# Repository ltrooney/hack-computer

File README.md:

The implementation files of the Hack Computer system. This current implementation uses the build instructions in the book The Elements of Computing Systems, by Noam Nisan and Shimon Schocken.

Programming languages used for: Hardware -> Hardware Description Language (HDL) --- Assembler, Virtual Machine (VM), and Compiler -> Java --- Operating System -> Jack

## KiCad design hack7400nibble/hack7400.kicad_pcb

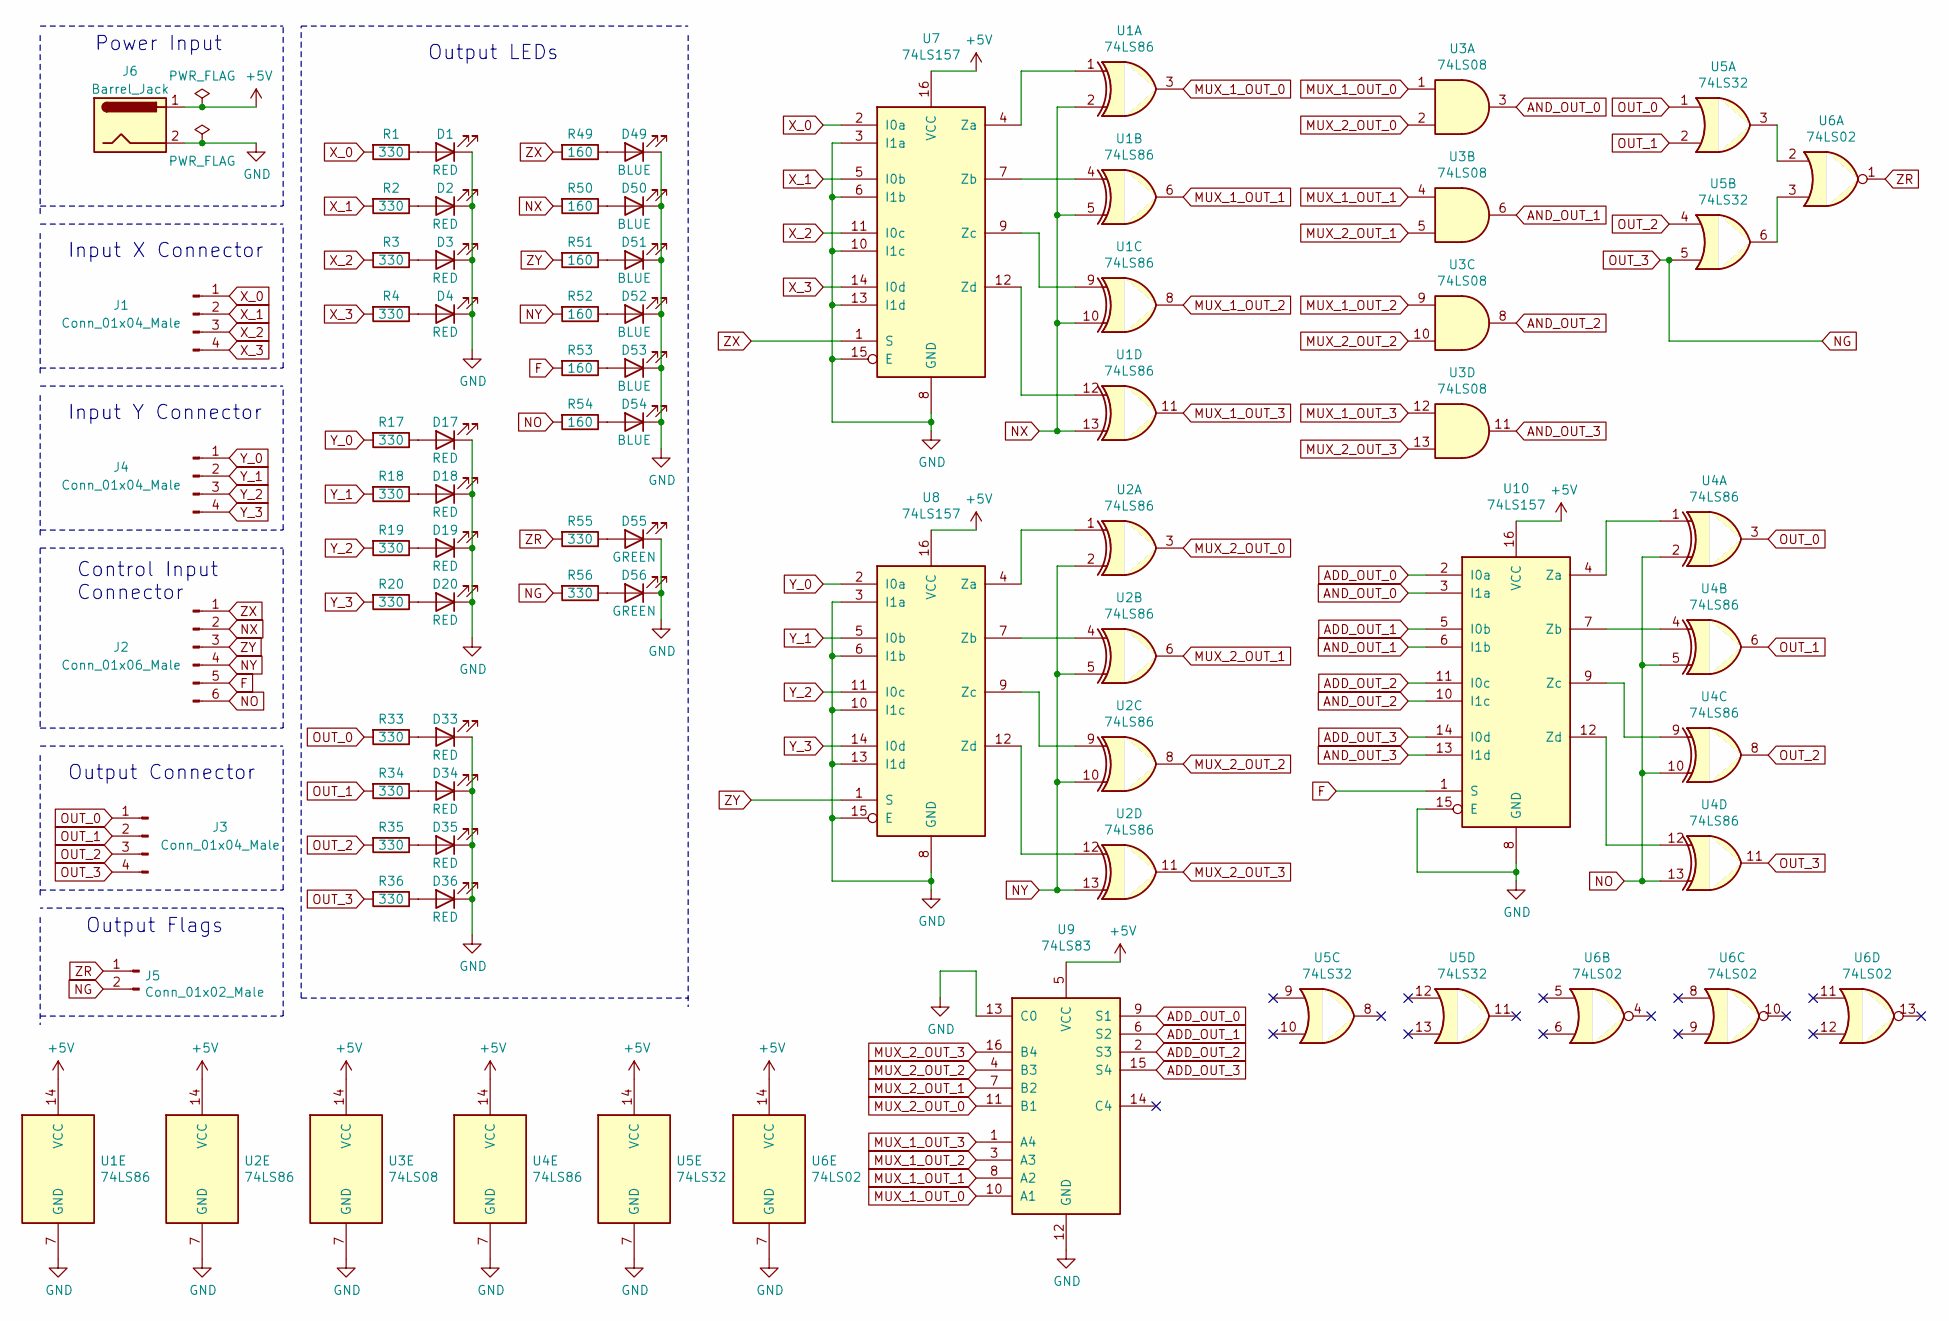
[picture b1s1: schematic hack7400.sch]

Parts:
D1, D2, D3, D4, D17, D18, D19, D20, D33, D34, D35, D36: RED; LED_D3.0mm
D49, D50, D51, D52, D53, D54: BLUE; LED_D3.0mm
D55, D56: GREEN; LED_D3.0mm
J1, J3, J4: Conn_01x04_Male; PinHeader_1x04_P2.54mm_Vertical
J2: Conn_01x06_Male; PinHeader_1x06_P2.54mm_Vertical
J5: Conn_01x02_Male; PinHeader_1x02_P2.54mm_Vertical
J6: Barrel_Jack; BarrelJack_CUI_PJ-102AH_Horizontal
R1, R2, R3, R4, R17, R18, R19, R20, R33, R34, R35, R36, R55, R56: 330; R_Axial_DIN0207_L6.3mm_D2.5mm_P7.62mm_Horizontal
R49, R50, R51, R52, R53, R54: 160; R_Axial_DIN0207_L6.3mm_D2.5mm_P7.62mm_Horizontal
U1, U2, U4: 74LS86; DIP-14_W7.62mm_Socket
U3: 74LS08; DIP-14_W7.62mm_Socket
U5: 74LS32; DIP-14_W7.62mm_Socket
U6: 74LS02; DIP-14_W7.62mm_Socket
U7, U8, U10: 74LS157; DIP-16_W7.62mm_Socket
U9: 74LS83; DIP-16_W7.62mm_Socket

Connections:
+5V: J6.1, U1.14 (VCC), U2.14 (VCC), U3.14 (VCC), U4.14 (VCC), U5.14 (VCC), U6.14 (VCC), U7.16 (VCC), U8.16 (VCC), U9.5 (VCC), U10.16 (VCC)
ADD_OUT_0: U9.9 (S1), U10.2 (I0a)
ADD_OUT_1: U9.6 (S2), U10.5 (I0b)
ADD_OUT_2: U9.2 (S3), U10.11 (I0c)
ADD_OUT_3: U9.15 (S4), U10.14 (I0d)
AND_OUT_0: U3.3, U10.3 (I1a)
AND_OUT_1: U3.6, U10.6 (I1b)
AND_OUT_2: U3.8, U10.10 (I1c)
AND_OUT_3: U3.11, U10.13 (I1d)
F: J2.5, R53.2, U10.1 (S)
GND: D1.1 (K), D2.1 (K), D3.1 (K), D4.1 (K), D17.1 (K), D18.1 (K), D19.1 (K), D20.1 (K), D33.1 (K), D34.1 (K), D35.1 (K), D36.1 (K), D49.1 (K), D50.1 (K), D51.1 (K), D52.1 (K), D53.1 (K), D54.1 (K), D55.1 (K), D56.1 (K), J6.2, U1.7 (GND), U2.7 (GND), U3.7 (GND), U4.7 (GND), U5.7 (GND), U6.7 (GND), U7.3 (I1a), U7.6 (I1b), U7.8 (GND), U7.10 (I1c), U7.13 (I1d), U7.15 (E), U8.3 (I1a), U8.6 (I1b), U8.8 (GND), U8.10 (I1c), U8.13 (I1d), U8.15 (E), U9.12 (GND), U9.13 (C0), U10.8 (GND), U10.15 (E)
MUX_1_OUT_0: U1.3, U3.1, U9.10 (A1)
MUX_1_OUT_1: U1.6, U3.4, U9.8 (A2)
MUX_1_OUT_2: U1.8, U3.9, U9.3 (A3)
MUX_1_OUT_3: U1.11, U3.12, U9.1 (A4)
MUX_2_OUT_0: U2.3, U3.2, U9.11 (B1)
MUX_2_OUT_1: U2.6, U3.5, U9.7 (B2)
MUX_2_OUT_2: U2.8, U3.10, U9.4 (B3)
MUX_2_OUT_3: U2.11, U3.13, U9.16 (B4)
NG: J3.4, J5.2, R36.2, R56.2, U4.11, U5.5
NO: J2.6, R54.2, U4.2, U4.5, U4.10, U4.13
NX: J2.2, R50.2, U1.2, U1.5, U1.10, U1.13
NY: J2.4, R52.2, U2.2, U2.5, U2.10, U2.13
unnamed: D1.2 (A), R1.1
unnamed: D2.2 (A), R2.1
unnamed: D3.2 (A), R3.1
unnamed: D4.2 (A), R4.1
unnamed: D17.2 (A), R17.1
unnamed: D18.2 (A), R18.1
unnamed: D19.2 (A), R19.1
unnamed: D20.2 (A), R20.1
unnamed: D33.2 (A), R33.1
unnamed: D34.2 (A), R34.1
unnamed: D35.2 (A), R35.1
unnamed: D36.2 (A), R36.1
unnamed: D49.2 (A), R49.1
unnamed: D50.2 (A), R50.1
unnamed: D51.2 (A), R51.1
unnamed: D52.2 (A), R52.1
unnamed: D53.2 (A), R53.1
unnamed: D54.2 (A), R54.1
unnamed: D55.2 (A), R55.1
unnamed: D56.2 (A), R56.1
unnamed: U1.1, U7.4 (Za)
unnamed: U1.4, U7.7 (Zb)
unnamed: U1.9, U7.9 (Zc)
unnamed: U1.12, U7.12 (Zd)
unnamed: U2.1, U8.4 (Za)
unnamed: U2.4, U8.7 (Zb)
unnamed: U2.9, U8.9 (Zc)
unnamed: U2.12, U8.12 (Zd)
unnamed: U5.3, U6.2
unnamed: U5.6, U6.3
unnamed: U4.1, U10.4 (Za)
unnamed: U4.4, U10.7 (Zb)
unnamed: U4.9, U10.9 (Zc)
unnamed: U4.12, U10.12 (Zd)
OUT_0: J3.1, R33.2, U4.3, U5.1
OUT_1: J3.2, R34.2, U4.6, U5.2
OUT_2: J3.3, R35.2, U4.8, U5.4
X_0: J1.1, R1.2, U7.2 (I0a)
X_1: J1.2, R2.2, U7.5 (I0b)
X_2: J1.3, R3.2, U7.11 (I0c)
X_3: J1.4, R4.2, U7.14 (I0d)
Y_0: J4.1, R17.2, U8.2 (I0a)
Y_1: J4.2, R18.2, U8.5 (I0b)
Y_2: J4.3, R19.2, U8.11 (I0c)
Y_3: J4.4, R20.2, U8.14 (I0d)
ZR: J5.1, R55.2, U6.1
ZX: J2.1, R49.2, U7.1 (S)
ZY: J2.3, R51.2, U8.1 (S)

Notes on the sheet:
Input X Connector
Control Input Connector
Output Flags
Output LEDs
Power Input
Input Y Connector
Output Connector

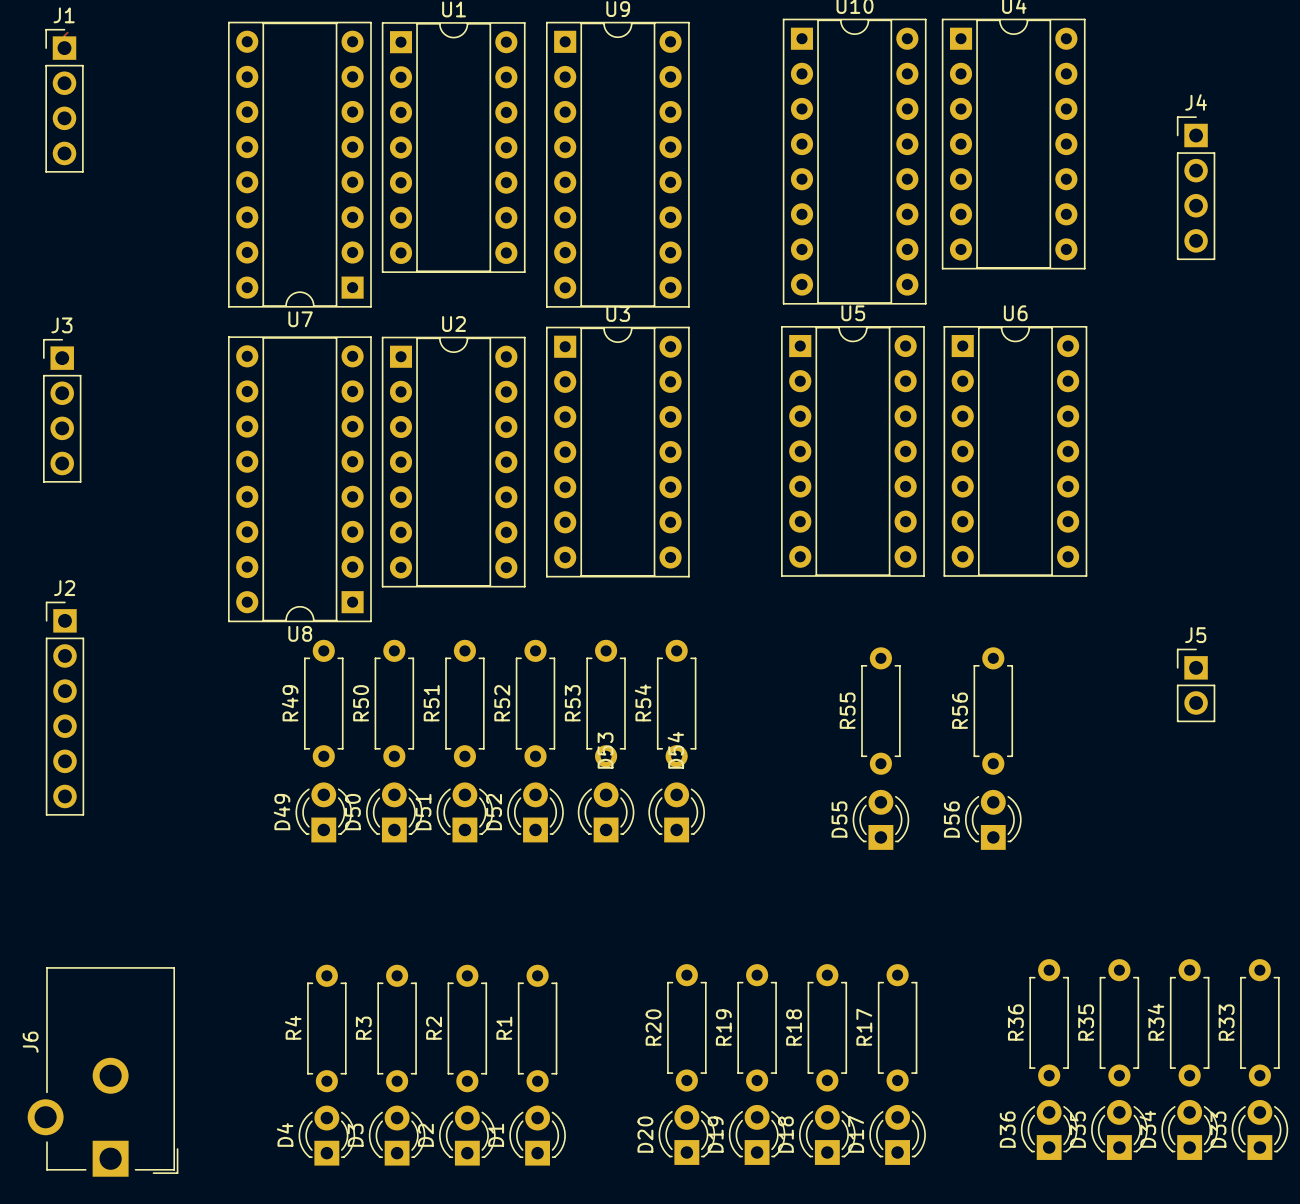
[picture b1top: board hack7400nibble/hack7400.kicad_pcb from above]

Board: 2 copper layers, 56 parts (0 on the bottom side), 71 nets.

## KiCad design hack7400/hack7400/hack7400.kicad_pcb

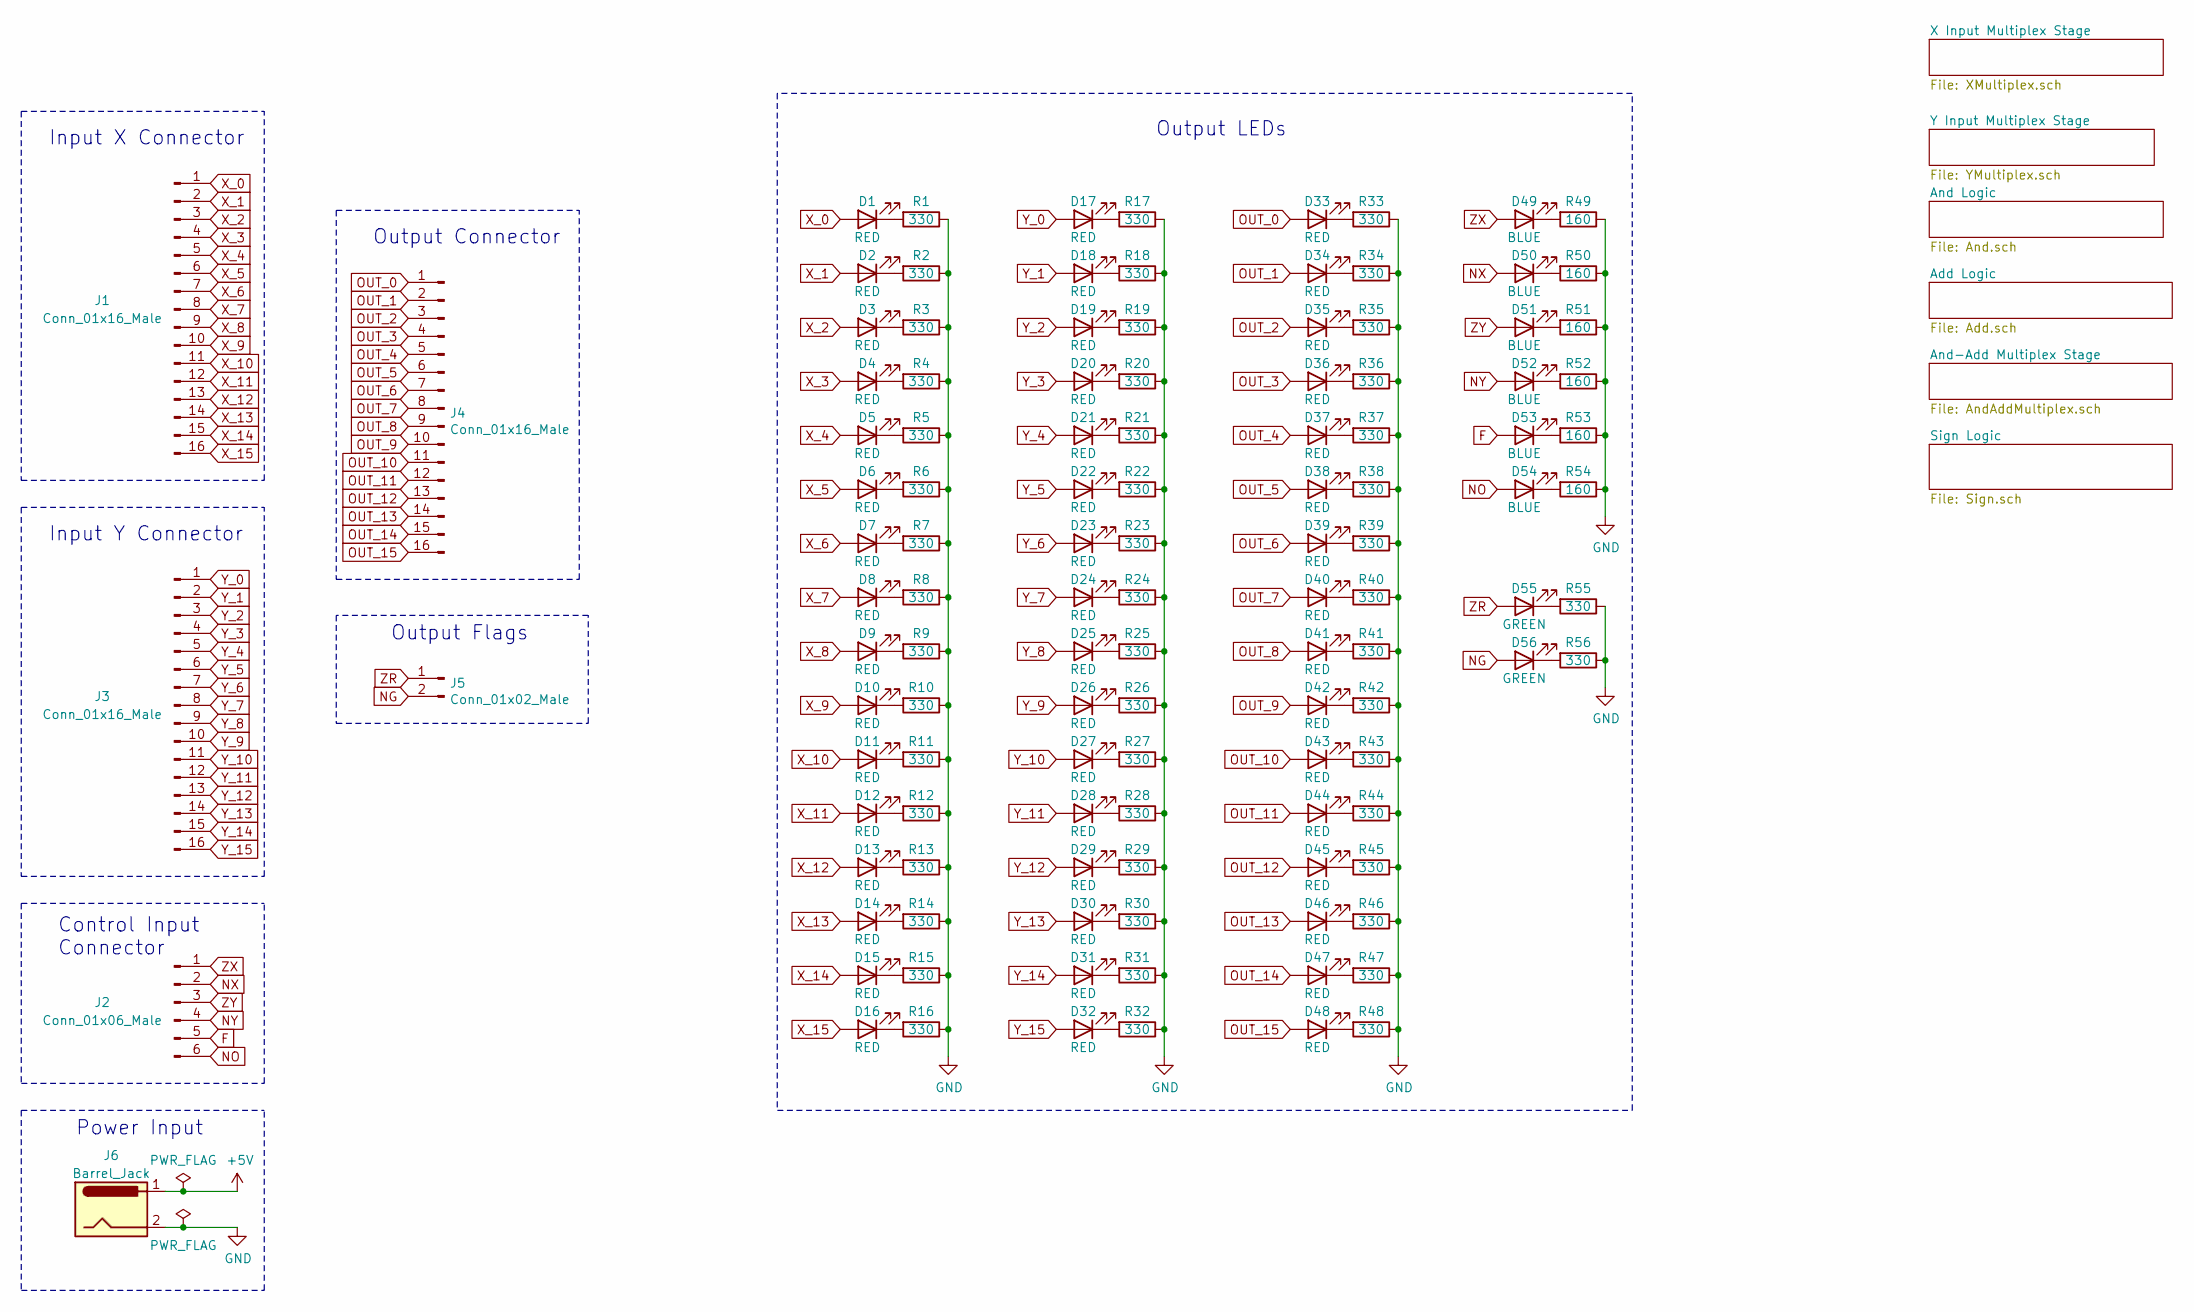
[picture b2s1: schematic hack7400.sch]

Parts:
D1, D2, D3, D4, D5, D6, D7, D8, D9, D10, D11, D12, D13, D14, D15, D16, D17, D18, D19, D20, D21, D22, D23, D24, D25, D26, D27, D28, D29, D30, D31, D32, D33, D34, D35, D36, D37, D38, D39, D40, D41, D42, D43, D44, D45, D46, D47, D48: RED; LED_D3.0mm
D49, D50, D51, D52, D53, D54: BLUE; LED_D3.0mm
D55, D56: GREEN; LED_D3.0mm
J1, J3, J4: Conn_01x16_Male; IDC-Header_2x08_P2.54mm_Vertical
J2: Conn_01x06_Male; PinHeader_1x06_P2.54mm_Vertical
J5: Conn_01x02_Male; PinHeader_1x02_P2.54mm_Vertical
J6: Barrel_Jack; BarrelJack_CUI_PJ-102AH_Horizontal
R1, R2, R3, R4, R5, R6, R7, R8, R9, R10, R11, R12, R13, R14, R15, R16, R17, R18, R19, R20, R21, R22, R23, R24, R25, R26, R27, R28, R29, R30, R31, R32, R33, R34, R35, R36, R37, R38, R39, R40, R41, R42, R43, R44, R45, R46, R47, R48, R55, R56: 330; R_Axial_DIN0207_L6.3mm_D2.5mm_P7.62mm_Horizontal
R49, R50, R51, R52, R53, R54: 160; R_Axial_DIN0207_L6.3mm_D2.5mm_P7.62mm_Horizontal

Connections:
+5V: J6.1; also elsewhere on the board
F: D53.2 (A), J2.5; also elsewhere on the board
GND: J6.2, R1.1, R2.1, R3.1, R4.1, R5.1, R6.1, R7.1, R8.1, R9.1, R10.1, R11.1, R12.1, R13.1, R14.1, R15.1, R16.1, R17.1, R18.1, R19.1, R20.1, R21.1, R22.1, R23.1, R24.1, R25.1, R26.1, R27.1, R28.1, R29.1, R30.1, R31.1, R32.1, R33.1, R34.1, R35.1, R36.1, R37.1, R38.1, R39.1, R40.1, R41.1, R42.1, R43.1, R44.1, R45.1, R46.1, R47.1, R48.1, R49.1, R50.1, R51.1, R52.1, R53.1, R54.1, R55.1, R56.1; also elsewhere on the board
NG: D48.2 (A), D56.2 (A), J4.16, J5.2; also elsewhere on the board
NO: D54.2 (A), J2.6; also elsewhere on the board
NX: D50.2 (A), J2.2; also elsewhere on the board
NY: D52.2 (A), J2.4; also elsewhere on the board
unnamed: D1.1 (K), R1.2
unnamed: D2.1 (K), R2.2
unnamed: D3.1 (K), R3.2
unnamed: D4.1 (K), R4.2
unnamed: D5.1 (K), R5.2
unnamed: D6.1 (K), R6.2
unnamed: D7.1 (K), R7.2
unnamed: D8.1 (K), R8.2
unnamed: D9.1 (K), R9.2
unnamed: D10.1 (K), R10.2
unnamed: D11.1 (K), R11.2
unnamed: D12.1 (K), R12.2
unnamed: D13.1 (K), R13.2
unnamed: D14.1 (K), R14.2
unnamed: D15.1 (K), R15.2
unnamed: D16.1 (K), R16.2
unnamed: D17.1 (K), R17.2
unnamed: D18.1 (K), R18.2
unnamed: D19.1 (K), R19.2
unnamed: D20.1 (K), R20.2
unnamed: D21.1 (K), R21.2
unnamed: D22.1 (K), R22.2
unnamed: D23.1 (K), R23.2
unnamed: D24.1 (K), R24.2
unnamed: D25.1 (K), R25.2
unnamed: D26.1 (K), R26.2
unnamed: D27.1 (K), R27.2
unnamed: D28.1 (K), R28.2
unnamed: D29.1 (K), R29.2
unnamed: D30.1 (K), R30.2
unnamed: D31.1 (K), R31.2
unnamed: D32.1 (K), R32.2
unnamed: D33.1 (K), R33.2
unnamed: D34.1 (K), R34.2
unnamed: D35.1 (K), R35.2
unnamed: D36.1 (K), R36.2
unnamed: D37.1 (K), R37.2
unnamed: D38.1 (K), R38.2
unnamed: D39.1 (K), R39.2
unnamed: D40.1 (K), R40.2
unnamed: D41.1 (K), R41.2
unnamed: D42.1 (K), R42.2
unnamed: D43.1 (K), R43.2
unnamed: D44.1 (K), R44.2
unnamed: D45.1 (K), R45.2
unnamed: D46.1 (K), R46.2
unnamed: D47.1 (K), R47.2
unnamed: D48.1 (K), R48.2
unnamed: D49.1 (K), R49.2
unnamed: D50.1 (K), R50.2
unnamed: D51.1 (K), R51.2
unnamed: D52.1 (K), R52.2
unnamed: D53.1 (K), R53.2
unnamed: D54.1 (K), R54.2
unnamed: D55.1 (K), R55.2
unnamed: D56.1 (K), R56.2
OUT_0: D33.2 (A), J4.1; also elsewhere on the board
OUT_1: D34.2 (A), J4.2; also elsewhere on the board
OUT_2: D35.2 (A), J4.3; also elsewhere on the board
OUT_3: D36.2 (A), J4.4; also elsewhere on the board
OUT_4: D37.2 (A), J4.5; also elsewhere on the board
OUT_5: D38.2 (A), J4.6; also elsewhere on the board
OUT_6: D39.2 (A), J4.7; also elsewhere on the board
OUT_7: D40.2 (A), J4.8; also elsewhere on the board
OUT_8: D41.2 (A), J4.9; also elsewhere on the board
OUT_9: D42.2 (A), J4.10; also elsewhere on the board
OUT_10: D43.2 (A), J4.11; also elsewhere on the board
OUT_11: D44.2 (A), J4.12; also elsewhere on the board
OUT_12: D45.2 (A), J4.13; also elsewhere on the board
OUT_13: D46.2 (A), J4.14; also elsewhere on the board
OUT_14: D47.2 (A), J4.15; also elsewhere on the board
X_0: D1.2 (A), J1.1; also elsewhere on the board
X_1: D2.2 (A), J1.2; also elsewhere on the board
X_2: D3.2 (A), J1.3; also elsewhere on the board
X_3: D4.2 (A), J1.4; also elsewhere on the board
X_4: D5.2 (A), J1.5; also elsewhere on the board
X_5: D6.2 (A), J1.6; also elsewhere on the board
X_6: D7.2 (A), J1.7; also elsewhere on the board
X_7: D8.2 (A), J1.8; also elsewhere on the board
X_8: D9.2 (A), J1.9; also elsewhere on the board
X_9: D10.2 (A), J1.10; also elsewhere on the board
X_10: D11.2 (A), J1.11; also elsewhere on the board
X_11: D12.2 (A), J1.12; also elsewhere on the board
X_12: D13.2 (A), J1.13; also elsewhere on the board
X_13: D14.2 (A), J1.14; also elsewhere on the board
X_14: D15.2 (A), J1.15; also elsewhere on the board
X_15: D16.2 (A), J1.16; also elsewhere on the board
Y_0: D17.2 (A), J3.1; also elsewhere on the board
Y_1: D18.2 (A), J3.2; also elsewhere on the board
Y_2: D19.2 (A), J3.3; also elsewhere on the board
Y_3: D20.2 (A), J3.4; also elsewhere on the board
Y_4: D21.2 (A), J3.5; also elsewhere on the board
Y_5: D22.2 (A), J3.6; also elsewhere on the board
Y_6: D23.2 (A), J3.7; also elsewhere on the board
Y_7: D24.2 (A), J3.8; also elsewhere on the board
Y_8: D25.2 (A), J3.9; also elsewhere on the board
Y_9: D26.2 (A), J3.10; also elsewhere on the board
Y_10: D27.2 (A), J3.11; also elsewhere on the board
Y_11: D28.2 (A), J3.12; also elsewhere on the board
Y_12: D29.2 (A), J3.13; also elsewhere on the board
Y_13: D30.2 (A), J3.14; also elsewhere on the board
Y_14: D31.2 (A), J3.15; also elsewhere on the board
Y_15: D32.2 (A), J3.16
ZR: D55.2 (A), J5.1; also elsewhere on the board
ZX: D49.2 (A), J2.1; also elsewhere on the board
ZY: D51.2 (A), J2.3; also elsewhere on the board

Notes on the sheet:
Input X Connector
Input Y Connector
Control Input Connector
Output Connector
Output Flags
Output LEDs
Power Input

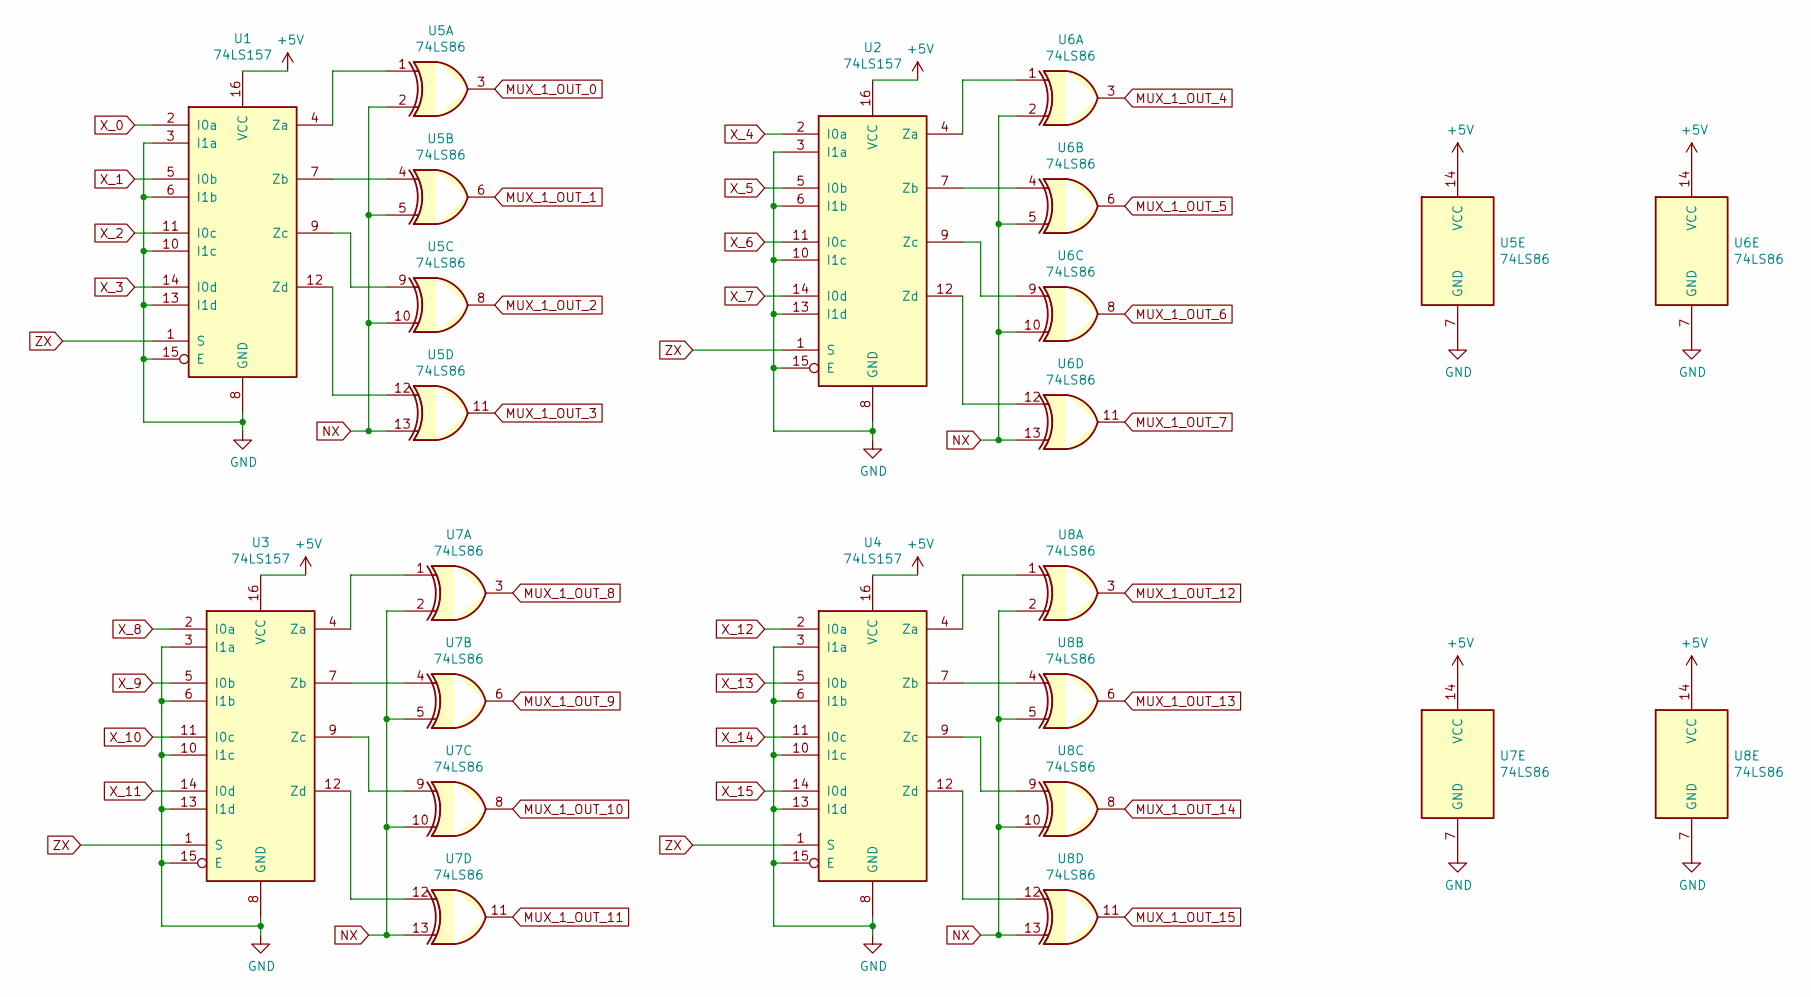
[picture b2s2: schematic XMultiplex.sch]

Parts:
U1, U2, U3, U4: 74LS157; DIP-16_W7.62mm_Socket
U5, U6, U7, U8: 74LS86; DIP-14_W7.62mm_Socket

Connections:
+5V: U1.16 (VCC), U2.16 (VCC), U3.16 (VCC), U4.16 (VCC), U5.14 (VCC), U6.14 (VCC), U7.14 (VCC), U8.14 (VCC); also elsewhere on the board
GND: U1.3 (I1a), U1.6 (I1b), U1.8 (GND), U1.10 (I1c), U1.13 (I1d), U1.15 (E), U2.3 (I1a), U2.6 (I1b), U2.8 (GND), U2.10 (I1c), U2.13 (I1d), U2.15 (E), U3.3 (I1a), U3.6 (I1b), U3.8 (GND), U3.10 (I1c), U3.13 (I1d), U3.15 (E), U4.3 (I1a), U4.6 (I1b), U4.8 (GND), U4.10 (I1c), U4.13 (I1d), U4.15 (E), U5.7 (GND), U6.7 (GND), U7.7 (GND), U8.7 (GND); also elsewhere on the board
MUX_1_OUT_0: U5.3; also elsewhere on the board
MUX_1_OUT_1: U5.6; also elsewhere on the board
MUX_1_OUT_2: U5.8; also elsewhere on the board
MUX_1_OUT_3: U5.11; also elsewhere on the board
MUX_1_OUT_4: U6.3; also elsewhere on the board
MUX_1_OUT_5: U6.6; also elsewhere on the board
MUX_1_OUT_6: U6.8; also elsewhere on the board
MUX_1_OUT_7: U6.11; also elsewhere on the board
MUX_1_OUT_8: U7.3; also elsewhere on the board
MUX_1_OUT_9: U7.6; also elsewhere on the board
MUX_1_OUT_10: U7.8; also elsewhere on the board
MUX_1_OUT_11: U7.11; also elsewhere on the board
MUX_1_OUT_12: U8.3; also elsewhere on the board
MUX_1_OUT_13: U8.6; also elsewhere on the board
MUX_1_OUT_14: U8.8; also elsewhere on the board
MUX_1_OUT_15: U8.11; also elsewhere on the board
NX: U5.2, U5.5, U5.10, U5.13, U6.2, U6.5, U6.10, U6.13, U7.2, U7.5, U7.10, U7.13, U8.2, U8.5, U8.10, U8.13; also elsewhere on the board
unnamed: U1.4 (Za), U5.1
unnamed: U1.7 (Zb), U5.4
unnamed: U1.9 (Zc), U5.9
unnamed: U1.12 (Zd), U5.12
unnamed: U2.4 (Za), U6.1
unnamed: U2.7 (Zb), U6.4
unnamed: U2.9 (Zc), U6.9
unnamed: U2.12 (Zd), U6.12
unnamed: U3.4 (Za), U7.1
unnamed: U3.7 (Zb), U7.4
unnamed: U3.9 (Zc), U7.9
unnamed: U3.12 (Zd), U7.12
unnamed: U4.4 (Za), U8.1
unnamed: U4.7 (Zb), U8.4
unnamed: U4.9 (Zc), U8.9
unnamed: U4.12 (Zd), U8.12
X_0: U1.2 (I0a); also elsewhere on the board
X_1: U1.5 (I0b); also elsewhere on the board
X_2: U1.11 (I0c); also elsewhere on the board
X_3: U1.14 (I0d); also elsewhere on the board
X_4: U2.2 (I0a); also elsewhere on the board
X_5: U2.5 (I0b); also elsewhere on the board
X_6: U2.11 (I0c); also elsewhere on the board
X_7: U2.14 (I0d); also elsewhere on the board
X_8: U3.2 (I0a); also elsewhere on the board
X_9: U3.5 (I0b); also elsewhere on the board
X_10: U3.11 (I0c); also elsewhere on the board
X_11: U3.14 (I0d); also elsewhere on the board
X_12: U4.2 (I0a); also elsewhere on the board
X_13: U4.5 (I0b); also elsewhere on the board
X_14: U4.11 (I0c); also elsewhere on the board
X_15: U4.14 (I0d); also elsewhere on the board
ZX: U1.1 (S), U2.1 (S), U3.1 (S), U4.1 (S); also elsewhere on the board

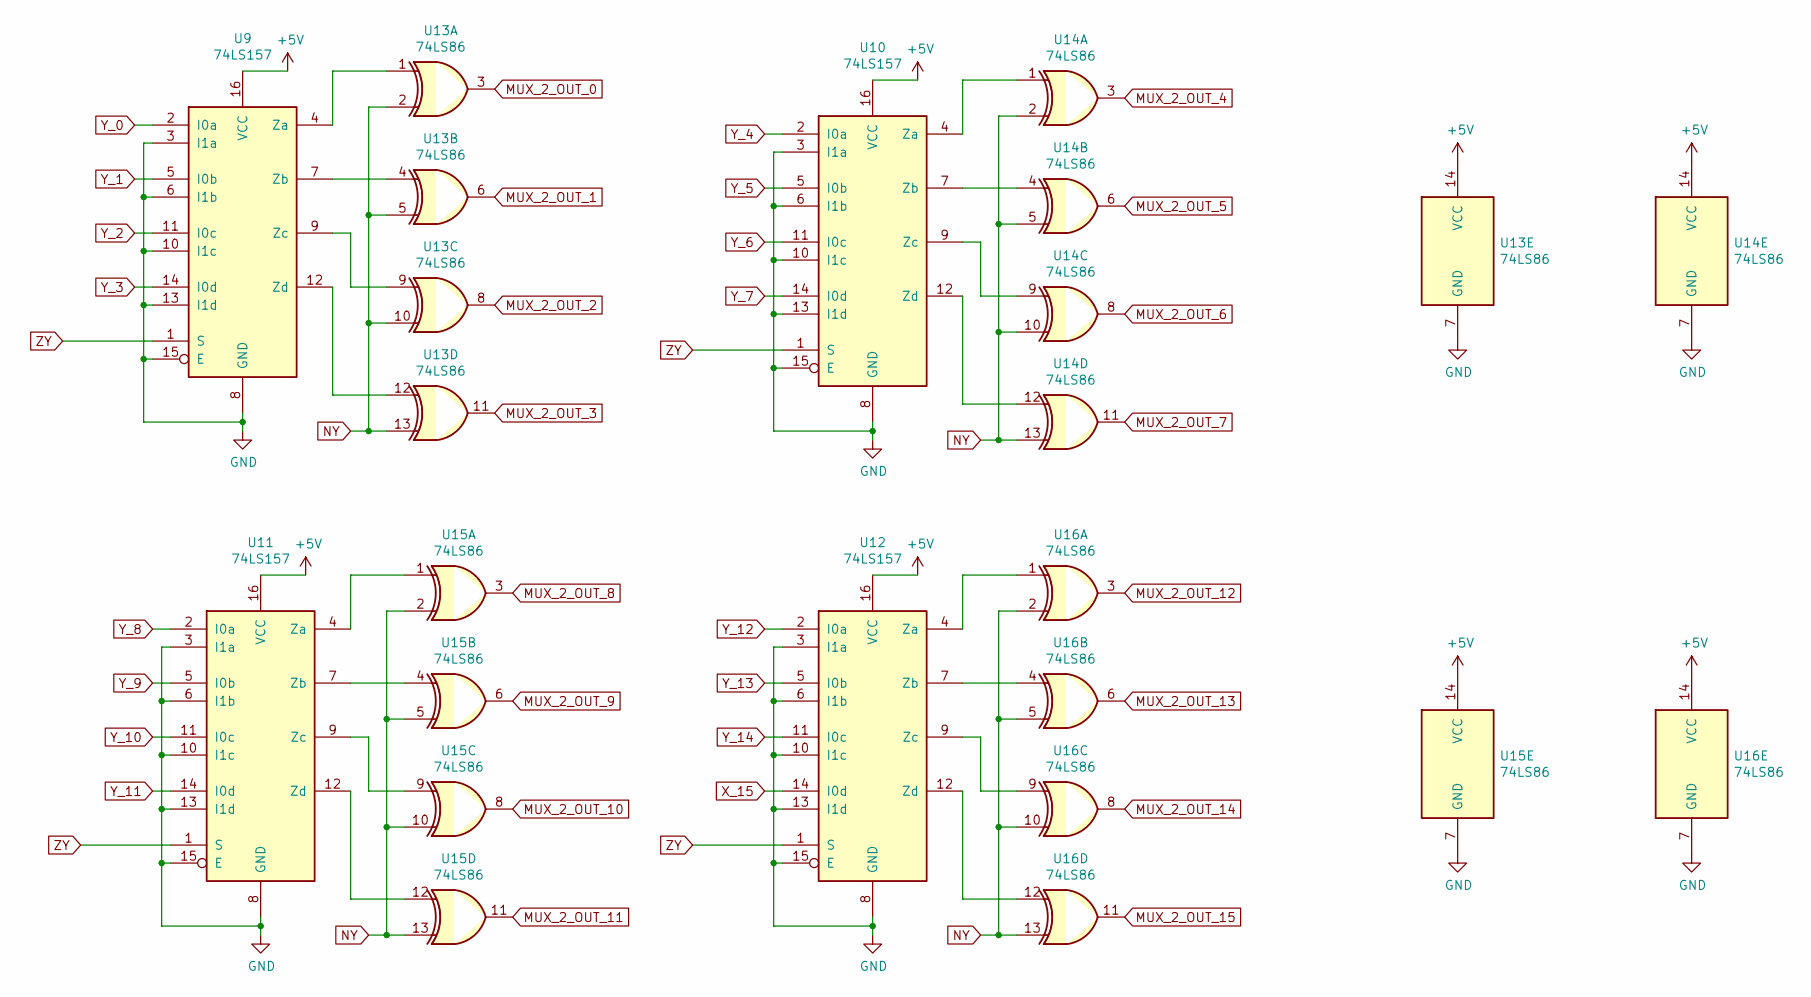
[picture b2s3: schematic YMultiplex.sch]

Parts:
U9, U10, U11, U12: 74LS157; DIP-16_W7.62mm_Socket
U13, U14, U15, U16: 74LS86; DIP-14_W7.62mm_Socket

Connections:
+5V: U9.16 (VCC), U10.16 (VCC), U11.16 (VCC), U12.16 (VCC), U13.14 (VCC), U14.14 (VCC), U15.14 (VCC), U16.14 (VCC); also elsewhere on the board
GND: U9.3 (I1a), U9.6 (I1b), U9.8 (GND), U9.10 (I1c), U9.13 (I1d), U9.15 (E), U10.3 (I1a), U10.6 (I1b), U10.8 (GND), U10.10 (I1c), U10.13 (I1d), U10.15 (E), U11.3 (I1a), U11.6 (I1b), U11.8 (GND), U11.10 (I1c), U11.13 (I1d), U11.15 (E), U12.3 (I1a), U12.6 (I1b), U12.8 (GND), U12.10 (I1c), U12.13 (I1d), U12.15 (E), U13.7 (GND), U14.7 (GND), U15.7 (GND), U16.7 (GND); also elsewhere on the board
MUX_2_OUT_0: U13.3; also elsewhere on the board
MUX_2_OUT_1: U13.6; also elsewhere on the board
MUX_2_OUT_2: U13.8; also elsewhere on the board
MUX_2_OUT_3: U13.11; also elsewhere on the board
MUX_2_OUT_4: U14.3; also elsewhere on the board
MUX_2_OUT_5: U14.6; also elsewhere on the board
MUX_2_OUT_6: U14.8; also elsewhere on the board
MUX_2_OUT_7: U14.11; also elsewhere on the board
MUX_2_OUT_8: U15.3; also elsewhere on the board
MUX_2_OUT_9: U15.6; also elsewhere on the board
MUX_2_OUT_10: U15.8; also elsewhere on the board
MUX_2_OUT_11: U15.11; also elsewhere on the board
MUX_2_OUT_12: U16.3; also elsewhere on the board
MUX_2_OUT_13: U16.6; also elsewhere on the board
MUX_2_OUT_14: U16.8; also elsewhere on the board
MUX_2_OUT_15: U16.11; also elsewhere on the board
NY: U13.2, U13.5, U13.10, U13.13, U14.2, U14.5, U14.10, U14.13, U15.2, U15.5, U15.10, U15.13, U16.2, U16.5, U16.10, U16.13; also elsewhere on the board
unnamed: U10.4 (Za), U14.1
unnamed: U10.7 (Zb), U14.4
unnamed: U10.9 (Zc), U14.9
unnamed: U10.12 (Zd), U14.12
unnamed: U11.4 (Za), U15.1
unnamed: U11.7 (Zb), U15.4
unnamed: U11.9 (Zc), U15.9
unnamed: U11.12 (Zd), U15.12
unnamed: U12.4 (Za), U16.1
unnamed: U12.7 (Zb), U16.4
unnamed: U12.9 (Zc), U16.9
unnamed: U12.12 (Zd), U16.12
unnamed: U9.4 (Za), U13.1
unnamed: U9.7 (Zb), U13.4
unnamed: U9.9 (Zc), U13.9
unnamed: U9.12 (Zd), U13.12
X_15: U12.14 (I0d); also elsewhere on the board
Y_0: U9.2 (I0a); also elsewhere on the board
Y_1: U9.5 (I0b); also elsewhere on the board
Y_2: U9.11 (I0c); also elsewhere on the board
Y_3: U9.14 (I0d); also elsewhere on the board
Y_4: U10.2 (I0a); also elsewhere on the board
Y_5: U10.5 (I0b); also elsewhere on the board
Y_6: U10.11 (I0c); also elsewhere on the board
Y_7: U10.14 (I0d); also elsewhere on the board
Y_8: U11.2 (I0a); also elsewhere on the board
Y_9: U11.5 (I0b); also elsewhere on the board
Y_10: U11.11 (I0c); also elsewhere on the board
Y_11: U11.14 (I0d); also elsewhere on the board
Y_12: U12.2 (I0a); also elsewhere on the board
Y_13: U12.5 (I0b); also elsewhere on the board
Y_14: U12.11 (I0c); also elsewhere on the board
ZY: U9.1 (S), U10.1 (S), U11.1 (S), U12.1 (S); also elsewhere on the board

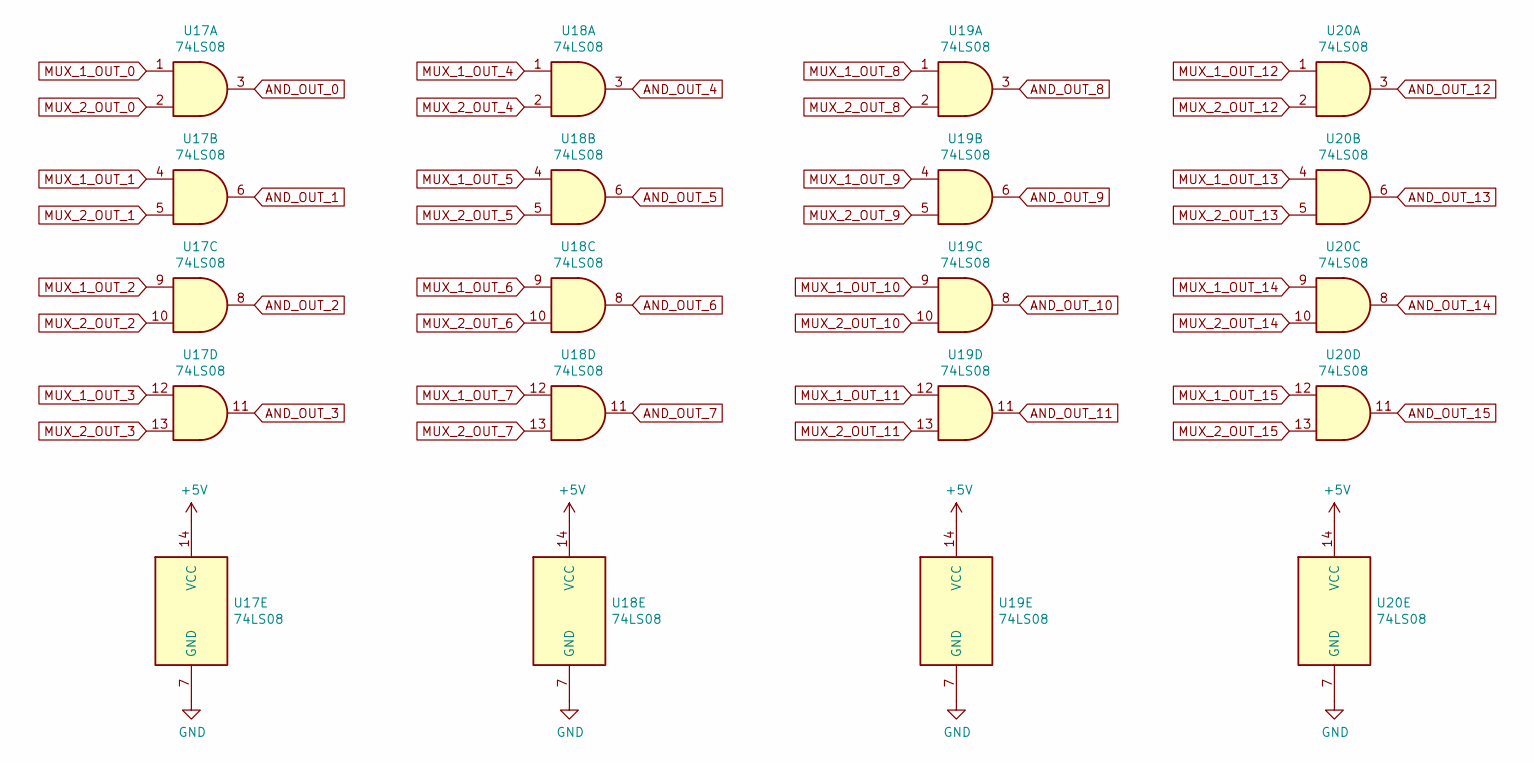
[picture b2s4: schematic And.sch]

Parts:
U17, U18, U19, U20: 74LS08; DIP-14_W7.62mm_Socket

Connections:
+5V: U17.14 (VCC), U18.14 (VCC), U19.14 (VCC), U20.14 (VCC); also elsewhere on the board
AND_OUT_0: U17.3; also elsewhere on the board
AND_OUT_1: U17.6; also elsewhere on the board
AND_OUT_2: U17.8; also elsewhere on the board
AND_OUT_3: U17.11; also elsewhere on the board
AND_OUT_4: U18.3; also elsewhere on the board
AND_OUT_5: U18.6; also elsewhere on the board
AND_OUT_6: U18.8; also elsewhere on the board
AND_OUT_7: U18.11; also elsewhere on the board
AND_OUT_8: U19.3; also elsewhere on the board
AND_OUT_9: U19.6; also elsewhere on the board
AND_OUT_10: U19.8; also elsewhere on the board
AND_OUT_11: U19.11; also elsewhere on the board
AND_OUT_12: U20.3; also elsewhere on the board
AND_OUT_13: U20.6; also elsewhere on the board
AND_OUT_14: U20.8; also elsewhere on the board
AND_OUT_15: U20.11; also elsewhere on the board
GND: U17.7 (GND), U18.7 (GND), U19.7 (GND), U20.7 (GND); also elsewhere on the board
MUX_1_OUT_0: U17.1; also elsewhere on the board
MUX_1_OUT_1: U17.4; also elsewhere on the board
MUX_1_OUT_2: U17.9; also elsewhere on the board
MUX_1_OUT_3: U17.12; also elsewhere on the board
MUX_1_OUT_4: U18.1; also elsewhere on the board
MUX_1_OUT_5: U18.4; also elsewhere on the board
MUX_1_OUT_6: U18.9; also elsewhere on the board
MUX_1_OUT_7: U18.12; also elsewhere on the board
MUX_1_OUT_8: U19.1; also elsewhere on the board
MUX_1_OUT_9: U19.4; also elsewhere on the board
MUX_1_OUT_10: U19.9; also elsewhere on the board
MUX_1_OUT_11: U19.12; also elsewhere on the board
MUX_1_OUT_12: U20.1; also elsewhere on the board
MUX_1_OUT_13: U20.4; also elsewhere on the board
MUX_1_OUT_14: U20.9; also elsewhere on the board
MUX_1_OUT_15: U20.12; also elsewhere on the board
MUX_2_OUT_0: U17.2; also elsewhere on the board
MUX_2_OUT_1: U17.5; also elsewhere on the board
MUX_2_OUT_2: U17.10; also elsewhere on the board
MUX_2_OUT_3: U17.13; also elsewhere on the board
MUX_2_OUT_4: U18.2; also elsewhere on the board
MUX_2_OUT_5: U18.5; also elsewhere on the board
MUX_2_OUT_6: U18.10; also elsewhere on the board
MUX_2_OUT_7: U18.13; also elsewhere on the board
MUX_2_OUT_8: U19.2; also elsewhere on the board
MUX_2_OUT_9: U19.5; also elsewhere on the board
MUX_2_OUT_10: U19.10; also elsewhere on the board
MUX_2_OUT_11: U19.13; also elsewhere on the board
MUX_2_OUT_12: U20.2; also elsewhere on the board
MUX_2_OUT_13: U20.5; also elsewhere on the board
MUX_2_OUT_14: U20.10; also elsewhere on the board
MUX_2_OUT_15: U20.13; also elsewhere on the board
